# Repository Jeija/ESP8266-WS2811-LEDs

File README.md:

# ESP8266 driver for WS2811 LED Strips
See the LED Strips in action in this video:

## Project description
This project uses the ESP8266's DMA (Direct Memory Access) functionality that is designed for I²S output in order to drive WS2811 LEDs. It is remotely based on cnlohr's [WS2812 driver implementation](https://github.com/cnlohr/esp8266ws2812i2s), but much more minimal. If you want to use this implementation in your own project, just get these source files:
* `firmware/src/ws2811dma.c`: Complete implementation of DMA WS2811 output
* `firmware/src/ws2811dma.h`: Header file contains important timing configuration
* `firmware/src/i2s_reg.h` and `firmware/src/slc_register.h`: Original source files from Espressif that contain register addresses for I²S and DMA functionality

If you want to know more about how DMA and I²S output actually works, I suggest you to watch cnlohr's [very informative video](https://www.youtube.com/watch?v=6zqGwxqJQnw) and read the source code.

The firmware will receive UDP packages on port 2711 with my custom, very simple MXP protocol (matrix protocol) that I originally made for [my LED Matrix project](https://github.com/Jeija/WS2811LEDMatrix). The node.js client provides a very simple user interface for live LJ'ing and is forked from the [LED Matrix client](https://github.com/Jeija/WS2811LEDMatrix).

Additionally, the ESP it will accept commands to turn the Voltek power supply on and off. You can easily send them with the following bash commands:
```bash
# Assuming 192.168.0.81 is the ESP8266's IP, port 2777 is default
# Disable the LED power supply
echo -e "\0"  >/dev/udp/192.168.0.81/2777

# Enable the LED power supply
echo -e "\1"  >/dev/udp/192.168.0.81/2777
```

## Build the Controller Hardware
I use an ESP-03 module on a custom board embedded into a "Voltek SPEC7188B" power supply for minimal usage of space and maximum portability. You can have a look at the KiCad PCB designs for the small, custom single-layered PCB that the ESP-03 mounts on top of in the `hardware` directory. Apart from adding a pin that can be used to enable / disable the power supply altogether it is just a very minimal way of interfacing the ESP-03 module.

The ESP8266 is basically powered by the trickle charge output of the Voltek power supply, so that it can manually toggle power for the LEDs connected to the strip. By default, it will enable the power supply.

Please mind that since this project is using DMA / I²S output, this will use up the RX pin of the ESP. I didn't experience any issues programming the module even when the LED strip was connected, but you might need to unplug the LEDs if this happens to you. The upside of this of course is that the RX pin is also available on popular modules like the ESP-01.

## Flash the Firmware
Before flashing the firmware, you will need to compile it with your own static network configuration. I use pfalcon's [esp-open-sdk](https://github.com/pfalcon/esp-open-sdk) as my ESP8266 build system. Depending the Espressif SDK version you are using, you might need to adjust the `SDK_DIR` setting in `firmware/Makefile`. Also, make sure the Xtensa build tools such as `xtensa-lx106-elf-gcc` and `xtensa-lx106-elf-gcc` as well as the themadinventor's [esptool](https://github.com/themadinventor/esptool) are in your `PATH`.

In order to compile the firmware with your network configuration, follow these steps:
* Go into the `firmware` directory
* `make clean` to get rid of any previous build of the firmware
* `make WIFI_SSID="myWifiSSID" WIFI_PASS="mySecretPassword" IP_ADDR="192.168.0.123" IP_SUBNET="255.255.0.0" flash`. Of course, you have to replace the SSID, password and IP placeholders with your network configuration.
* Connect the ESP8266 and choose your preffered baudrate and port in `firmware/Makefile`. If you don't use DTR/RTS to get the ESP into programming mode, you need to manually enter flash download mode now.
* `make flash` to download the firmware

The ESP should now try to connect to your WiFi network. If the WS2811 LED strip is connected, it will light up the first 10 LEDs red while connecting and green as soon as the connection has been established.

## Install and use the client
The node.js client allows for live input of animation data (e.g. corresponding to music). It has an animation queue that can be put together by multiple people at once and a site for the LED strip operator / LJ with a live preview of the current colors on the LED strips.

* Install dependencies: You need to have `node.js`, `npm` and `bower` installed on your system. Go to `client` and execute `npm install` to install all dependencies. Then, install the bower dependencies by executing `bower install` in `client/site`.
* You should edit the file `client/config.json` to reflect the actual LED strip configuration you are using.
* You can run the node.js server by executing `client/server.js`: In the `client` directory, type `node server.js`.
* The server is now available at [localhost:8080](http://localhost:8080) or at any IP of your computer. You can manage the animation queue at [localhost:8080/queue](http://localhost:8080/queue) and execute queue elements and control the animation at [localhost:8080](http://localhost:8080). On that page, press the `n` key to start the next animation, and any of the keys `a`, `s`, `d` or `f` for rhythm input. You can toggle the recording feature that records keypresses with the `r` key and play back your recordings by pressing `p`.

For animations that use the spectrum analyzer, the animation server must get good quality music input from the default microphone or line in device. Music input also requires ALSA and its tools to be installed on the server machine!

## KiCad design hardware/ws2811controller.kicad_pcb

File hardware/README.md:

## Hardware Design
### Notes
The Hardware design uses the prebuilt ESP-03 modules for quicker assembly and cost-effectiveness. Since the hardware module is designed to fit into the "Voltek SPEC7188B" and is supposed to be used with a single layer PCB, you will have to solder a connection from the resistor on the top left to CH_PD manually. I also recommend to solder a wire with a length of 12.5cm to the antenna pin of the ESP-03 as a WiFi aerial for better signal reception.

### Attribution
* `mod/esp-03` and `lib/esp-03` were originally designed by (myelin)[https://github.com/myelin]

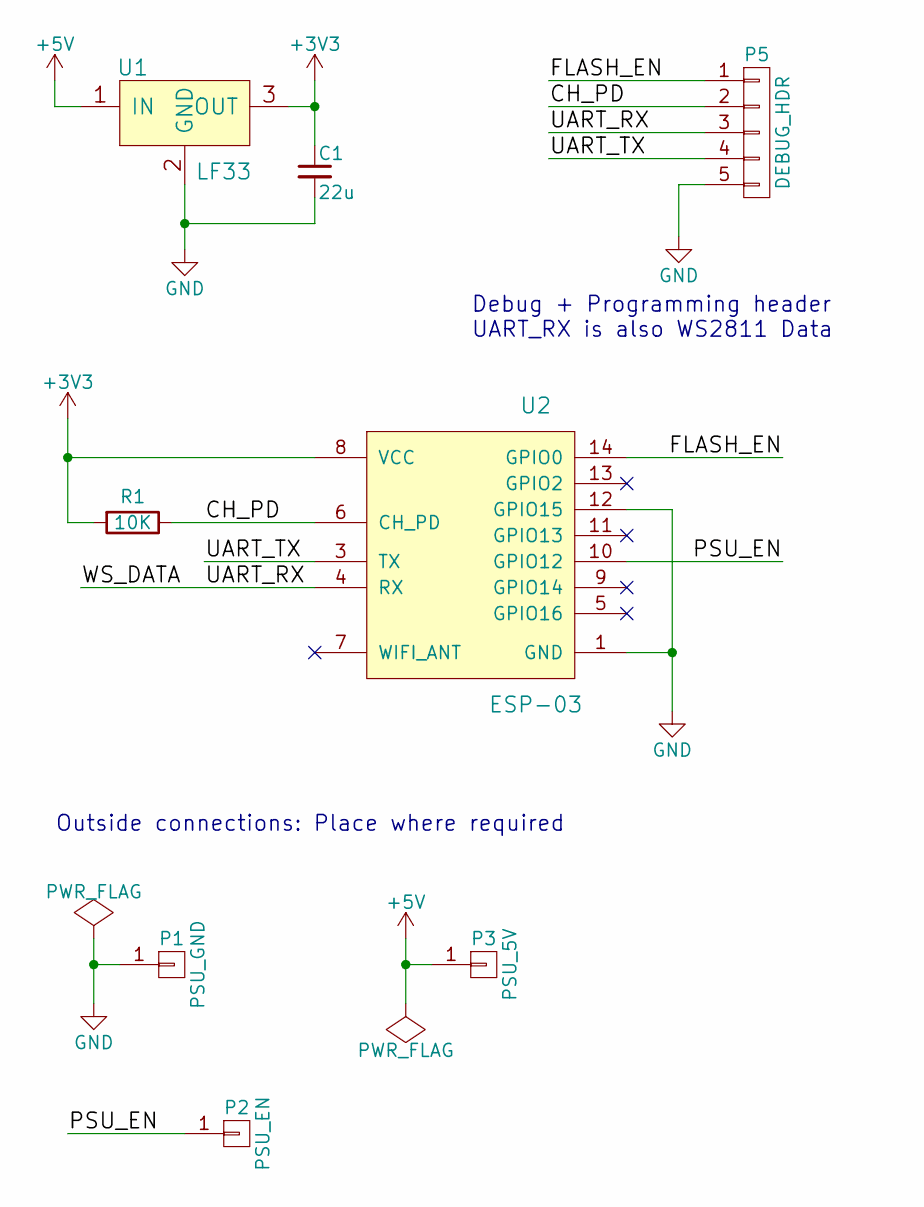
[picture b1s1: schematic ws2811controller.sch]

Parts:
C1: 22u; C_1206_HandSoldering
P1: PSU_GND; SolderPad
P2: PSU_EN; SolderPad
P3: PSU_5V; SolderPad
P5: DEBUG_HDR; 5pin_SMD
R1: 10K; R_1206_HandSoldering
U1: LF33; TO-252-2Lead
U2: ESP-03; esp-03

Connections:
+3V3: C1.1, R1.2, U1.3 (OUT), U2.8 (VCC)
+5V: P3.1, U1.1 (IN)
/CH_PD: P5.2, R1.1, U2.6 (CH_PD)
/FLASH_EN: P5.1, U2.14 (GPIO0)
/PSU_EN: P2.1, U2.10 (GPIO12)
/UART_RX: P5.3, U2.4 (RX)
/UART_TX: P5.4, U2.3 (TX)
GND: C1.2, P1.1, P5.5, U1.2 (GND), U2.1 (GND), U2.12 (GPIO15)

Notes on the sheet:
Debug + Programming header UART_RX is also WS2811 Data
Outside connections: Place where required

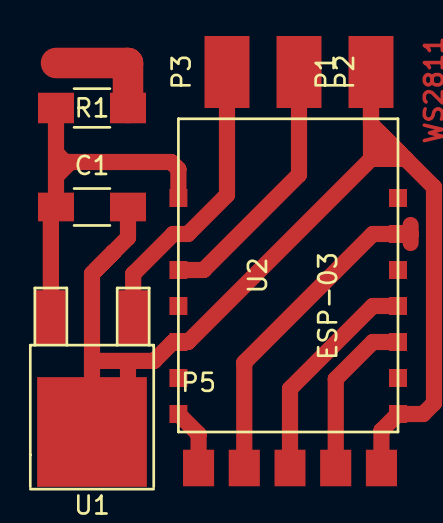
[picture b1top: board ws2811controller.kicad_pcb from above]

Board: 2 copper layers, 8 parts (0 on the bottom side), 8 nets.

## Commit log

2016-01-24 Initial Upload
2016-01-26 Add two more effects: Colorband and darknoise
2016-01-31 Add single-color animation
2016-01-31 Add spectrum animation
2016-01-31 Fix bugs in spectrum code and clean config
2016-02-01 Spectrum: Tweak parameters Change server port to 8081
2016-02-01 Add animations: Pulsate and skynoise
2016-02-02 Add colorful and firenoise effects, start work on particles effect, fix client canvas size
2016-02-03 Finish particles animation and add wave animation
2016-02-03 Client: Enable CORS to allow for receiving events via GET request
2016-02-03 Add more shortcuts, fix minor issues
2016-02-04 Add heatnoise and rainbow dash noise animations
2016-02-26 Add video to README and update config.json
2016-11-27 Client: Update package.json for latest dependencies
